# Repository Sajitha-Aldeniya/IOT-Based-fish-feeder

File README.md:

# **IOT Based fish feeder**
---
## **Introduction**

The IOT Based fish feeder is a small device which is design for aquarium industry. Specially for the small and lag scale fish farms, which need lot of man power to feed the fish in time. This is one of the biggest challenge face by the fish farm owners. This device will helps to feed the fish in time. The IOT based fish feeder is consists of two parts, the hardware and a mobile application to setup and control the device. The following topic will cover these parts in farther more details and also the operation of the device.  

## **1. Mobile Application**

The mobile application is build by using the Blink IOT platform. It is a very nice platform which helps to create mobile applications for IOT projects without any needs of app development knowledge. The following figure show the screenshot of my prototype app.

The slider at the top use to control the amount of food feed to the fish tank. At the bottom of the app there is a button to feed the fish manually. By pressing this button the device will put fish food manually to tank. In middle the application there are 3 timers which can set accordingly by user. There are three timers on this app.

## **2. Hardware**      
 The hardware part also can be divided in to two parts. Mechanical design and Electrical design.

### **2.1 Mechanical design**

The mechanical design part contain all the mechanical system and the enclosure of the device. Mainly there are 5 parts in the mechanical system.

1. Body
1. Bottom Plate
1. Segmented Wheel
1. Back Plate
1. Lid

Following images show the individual CAD design of each part.

1. Body

2. Bottom Plate

3. Segmented Wheel

4. Back Plate

5. Lid

### **2.2 Electrical design**

1. BOM of the electrical design.
1. 24BYJ48 DC 5V Reduction Stepper Motor
1. UL2003
1. LED
1. IR LED
1. IR photo diode.
1. 2N7000 MOSFET
1. ESP8266
1. AMS1117 3.3
1. 100uF Capacitors
1. 50k potentiometer 
1. 300 Resistor
1. 10k Resistor
1. Pin Headers.

The Stepper motor is fixed to body. All the other components are placed on a PCB. 5V needed for the PCB to properly operate. This 5V is given by a external power source.  The PCB is a single layer PCB. The  following images shows the PCB design. and the prototype PCB.

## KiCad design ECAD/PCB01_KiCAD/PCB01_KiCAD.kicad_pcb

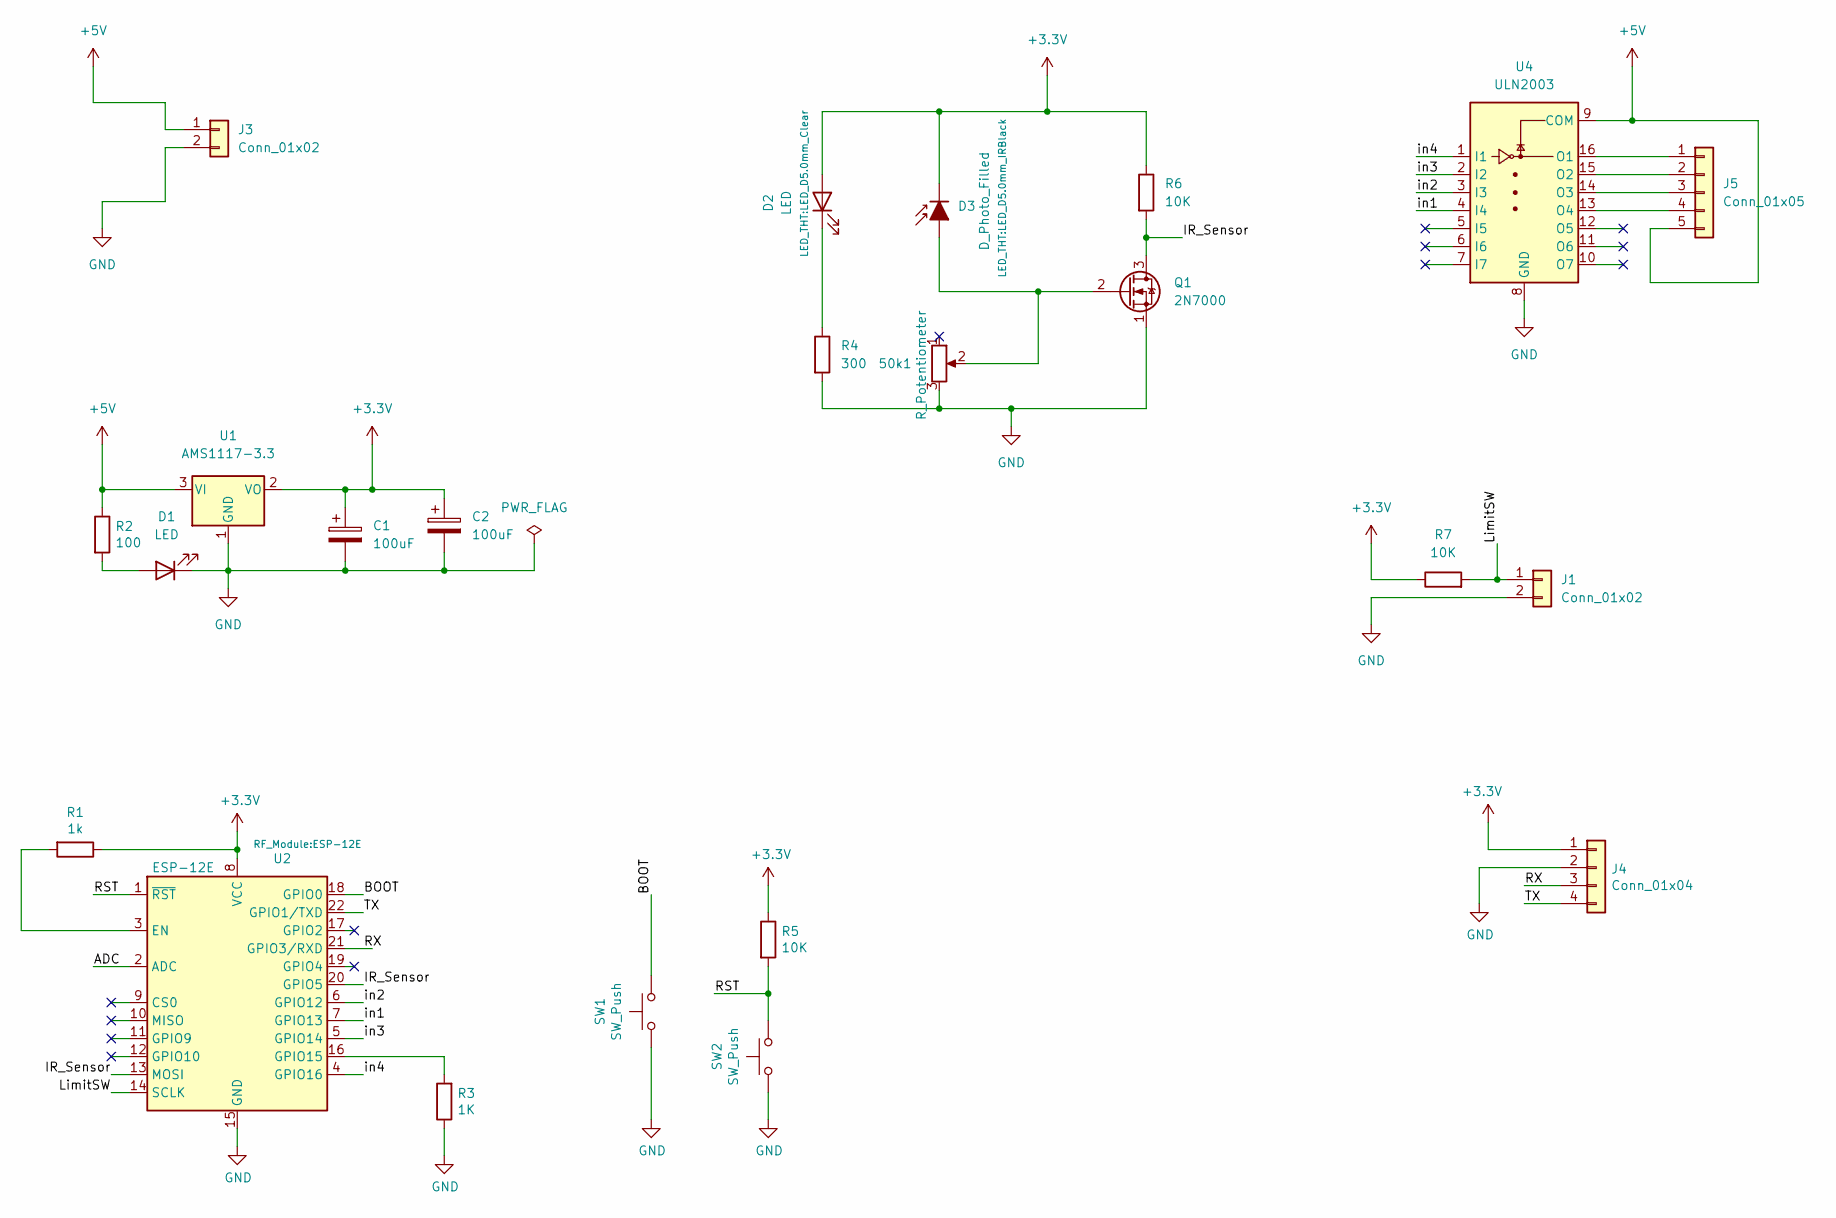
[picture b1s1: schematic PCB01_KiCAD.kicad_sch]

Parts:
50k1: R_Potentiometer; Potentiometer_Runtron_RM-065_Vertical
C1, C2: 100uF; CP_Radial_D5.0mm_P2.50mm
D1: LED; LED_1206_3216Metric_Pad1.42x1.75mm_HandSolder
D2: LED; LED_D5.0mm_Clear
D3: D_Photo_Filled; LED_D5.0mm_IRBlack
J1, J3: Conn_01x02; JST_PH_B2B-PH-K_1x02_P2.00mm_Vertical
J4: Conn_01x04; PinHeader_1x04_P2.54mm_Horizontal
J5: Conn_01x05; PinHeader_1x05_P2.54mm_Vertical
Q1: 2N7000; TO-92L_Inline_Wide
R1: 1k; R_1206_3216Metric_Pad1.30x1.75mm_HandSolder
R2: 100; R_1206_3216Metric_Pad1.30x1.75mm_HandSolder
R3: 1K; R_1206_3216Metric_Pad1.30x1.75mm_HandSolder
R4: 300; R_Axial_DIN0207_L6.3mm_D2.5mm_P10.16mm_Horizontal
R5: 10K; R_1206_3216Metric_Pad1.30x1.75mm_HandSolder
R6, R7: 10K; R_Axial_DIN0207_L6.3mm_D2.5mm_P10.16mm_Horizontal
SW1, SW2: SW_Push; SW_SPST_CK_RS282G05A3
U1: AMS1117-3.3; SOT-223-3_TabPin2
U2: ESP-12E
U4: ULN2003; DIP-16_W7.62mm_LongPads

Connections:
+3V3: C1.1, C2.1, D2.2 (A), D3.1 (K), J4.1, R1.1, R5.1, R6.1, R7.1, U1.2 (VO), U2.8 (VCC)
+5V: J3.1, J5.5, R2.1, U1.3 (VI), U4.9 (COM)
/BOOT: SW1.2, U2.18 (GPIO0)
/IR_Sensor: Q1.3 (D), R6.2, U2.13 (MOSI), U2.20 (GPIO5)
/LimitSW: J1.1, R7.2, U2.14 (SCLK)
/RST: R5.2, SW2.2, U2.1 (~RST)
/RX: J4.3, U2.21 (GPIO3/RXD)
/TX: J4.4, U2.22 (GPIO1/TXD)
/in1: U2.7 (GPIO13), U4.4 (I4)
/in2: U2.6 (GPIO12), U4.3 (I3)
/in3: U2.5 (GPIO14), U4.2 (I2)
/in4: U2.4 (GPIO16), U4.1 (I1)
GND: 50k1.3, C1.2, C2.2, D1.1 (K), J1.2, J3.2, J4.2, Q1.1 (S), R3.1, R4.2, SW1.1, SW2.1, U1.1 (GND), U2.15 (GND), U4.8 (GND)
unnamed: 50k1.2, D3.2 (A), Q1.2 (G)
unnamed: D1.2 (A), R2.2
unnamed: D2.1 (K), R4.1
unnamed: J5.1, U4.16 (O1)
unnamed: J5.2, U4.15 (O2)
unnamed: J5.3, U4.14 (O3)
unnamed: J5.4, U4.13 (O4)
unnamed: R1.2, U2.3 (EN)
unnamed: R3.2, U2.16 (GPIO15)

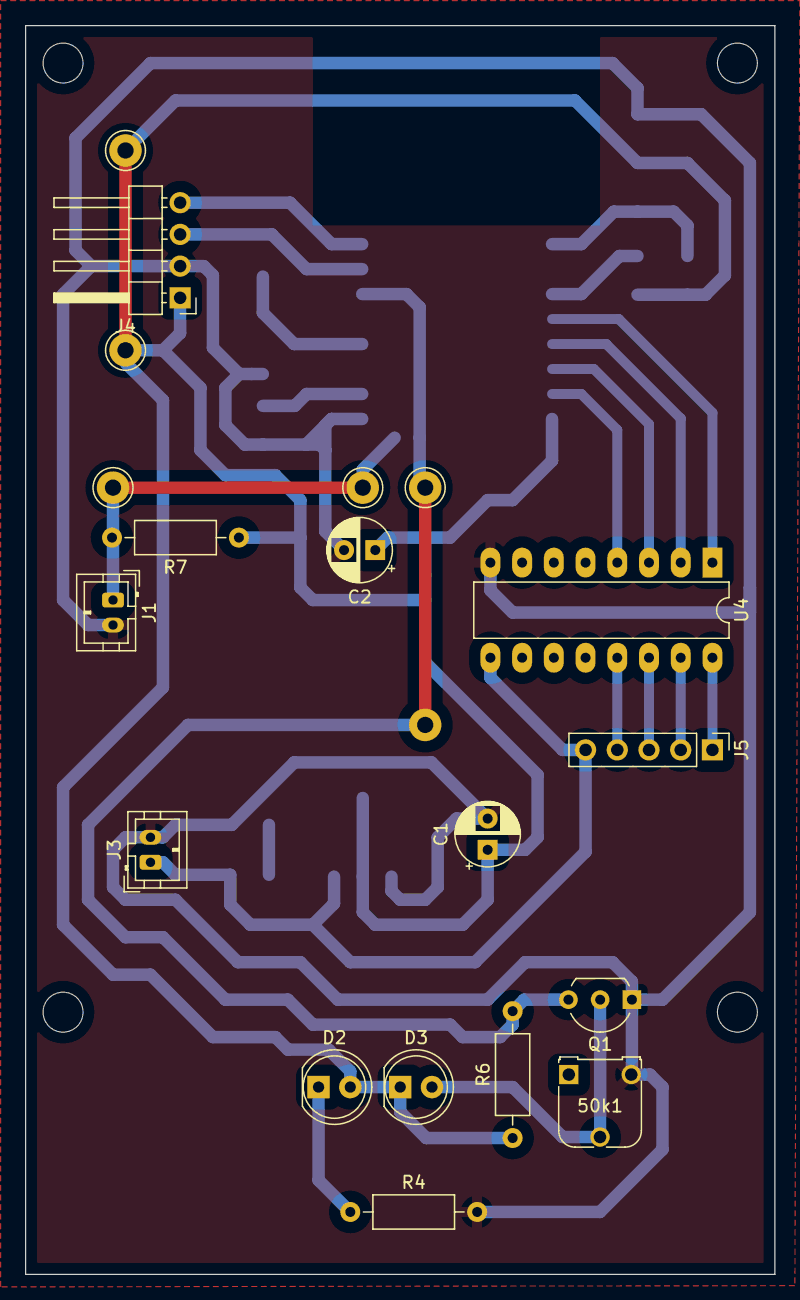
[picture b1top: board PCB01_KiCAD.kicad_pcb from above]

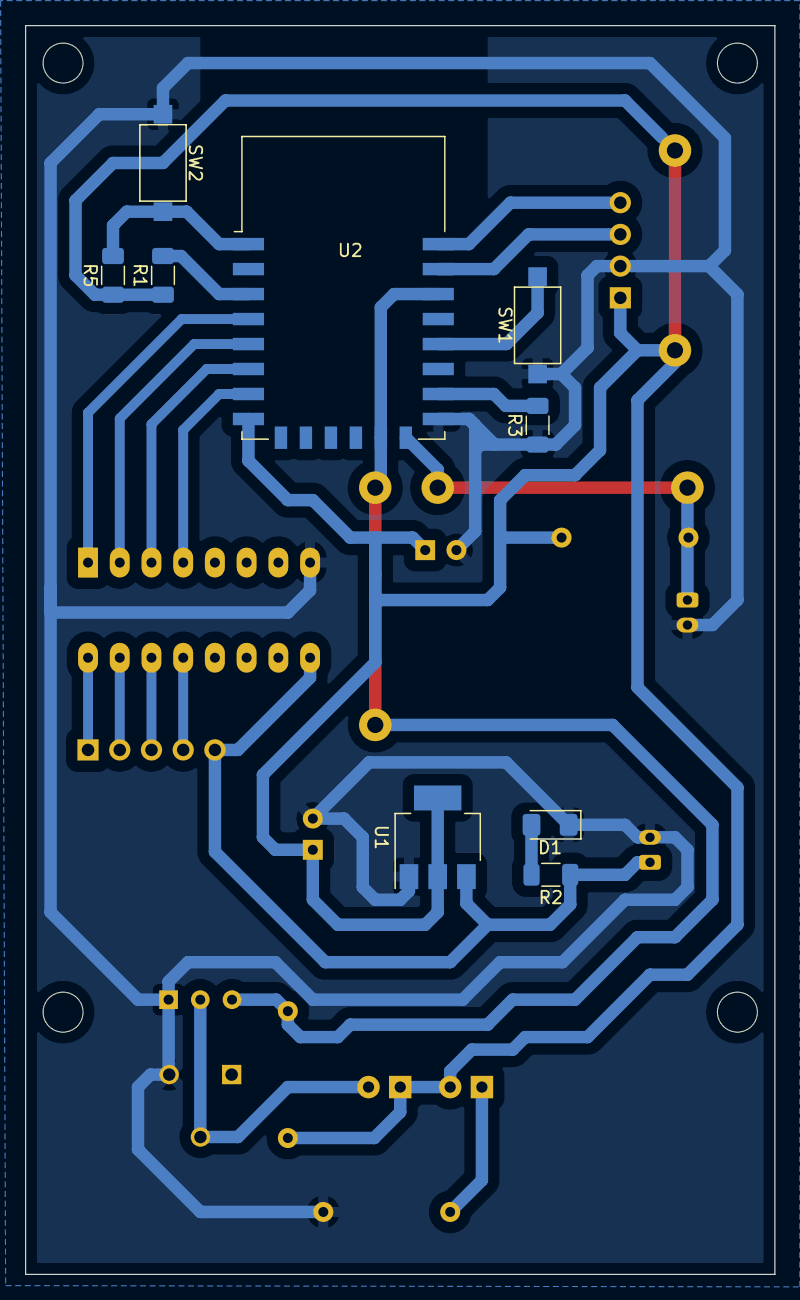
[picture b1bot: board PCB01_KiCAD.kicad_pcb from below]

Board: 2 copper layers, 60.0 x 100.0 mm, 23 parts (9 on the bottom side), 22 nets.

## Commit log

2021-11-09 Commiting the edit Readme
